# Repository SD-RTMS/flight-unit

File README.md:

# flight-unit

flight unit hardware and software

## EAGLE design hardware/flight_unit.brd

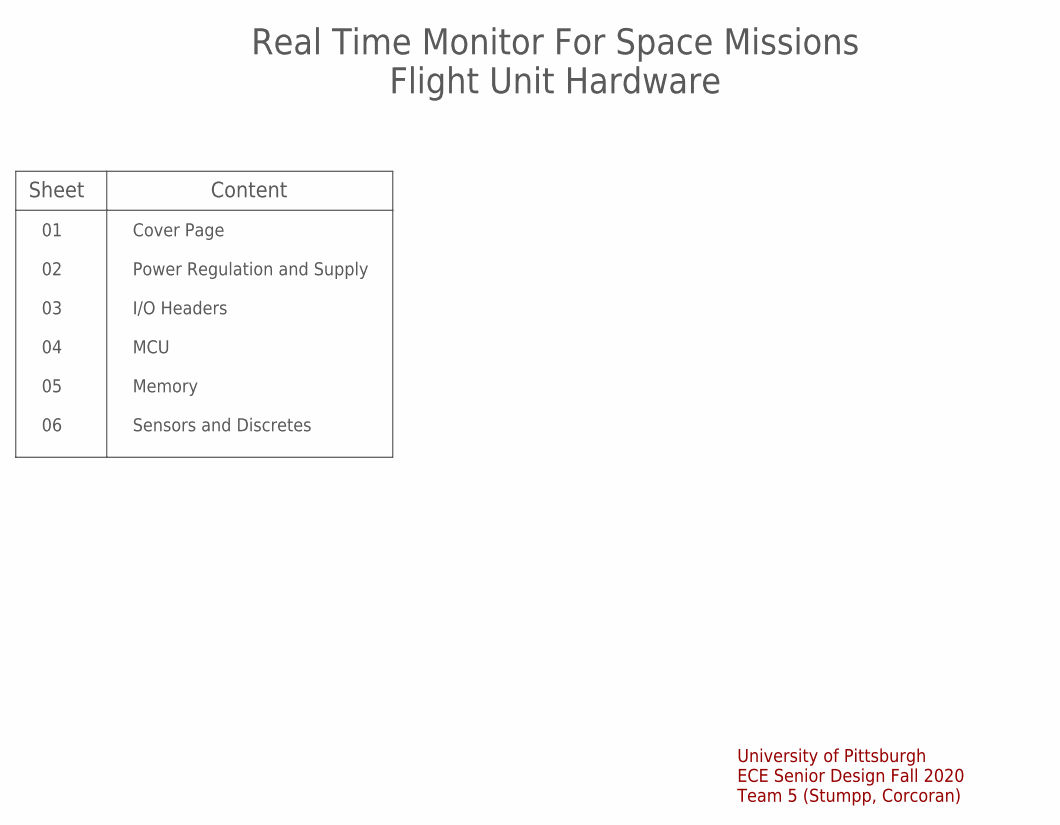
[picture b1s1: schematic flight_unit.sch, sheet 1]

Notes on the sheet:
University of Pittsburgh ECE Senior Design Fall 2020 Team 5 (Stumpp, Corcoran)
Real Time Monitor For Space Missions Flight Unit Hardware
Content
01 02 03 04 05 06
Cover Page Power Regulation and Supply I/O Headers MCU Memory Sensors and Discretes
Sheet

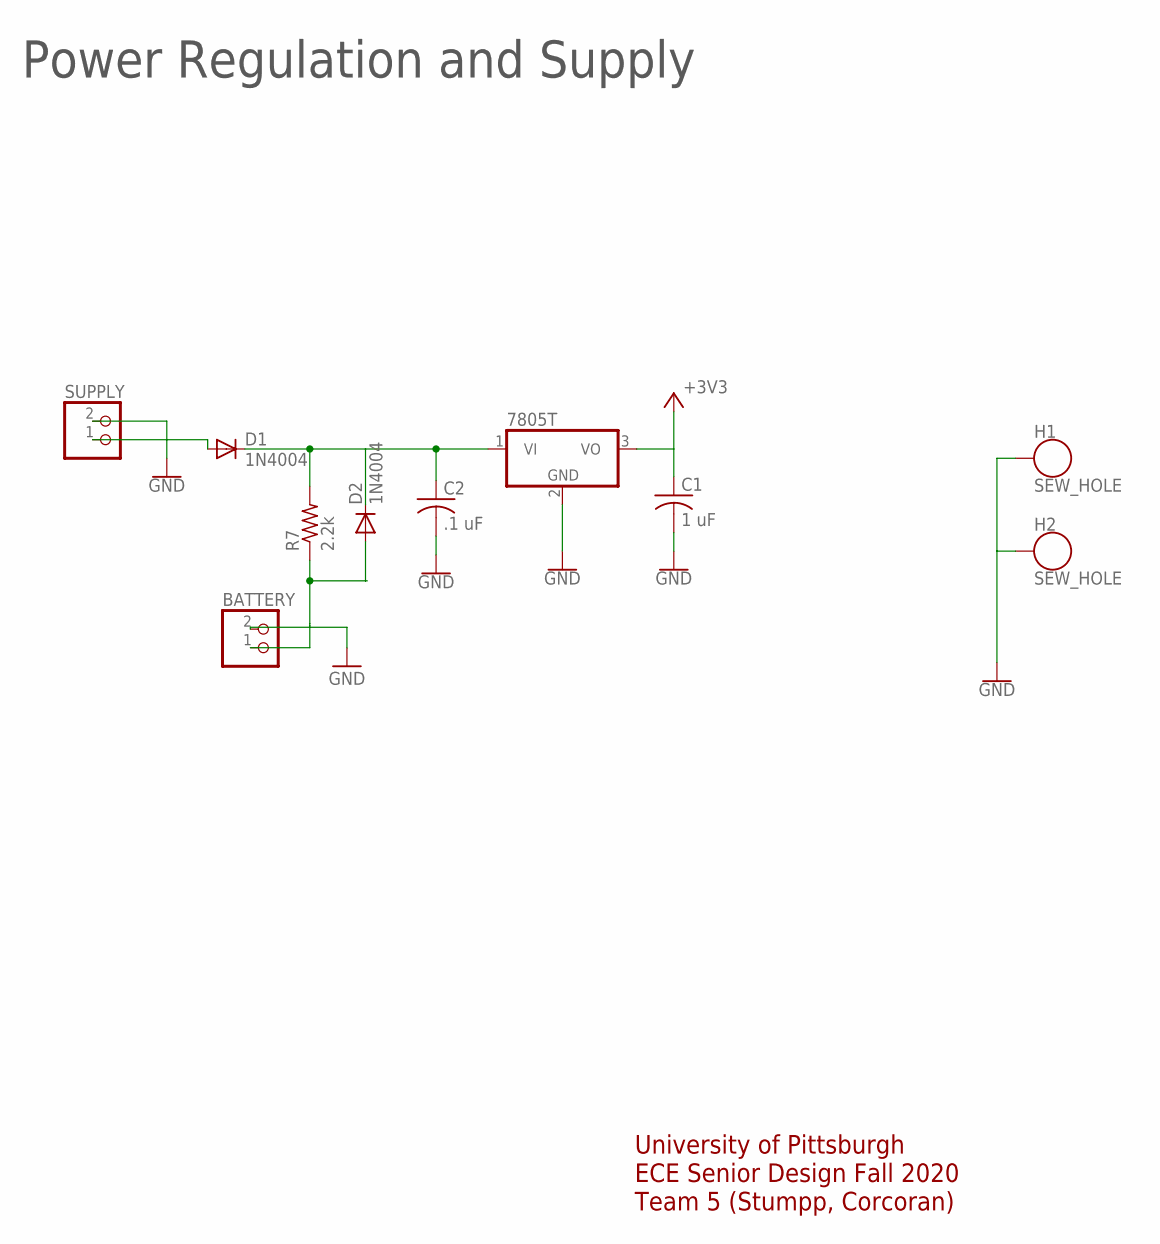
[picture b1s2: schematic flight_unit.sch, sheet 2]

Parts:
BATTERY: JST_2PIN-THM; JST-PH-2-THM
C1: 1 uF; C0805K
C2: .1 uF; C0805K
D1, D2: 1N4004; DO41-10
H1, H2: SEW_HOLE; SIMPLE_HOLE
IC2: 7805T; TO220H
R7: 2.2k; R0805
SUPPLY: JST_2PIN-THM; JST-PH-2-THM

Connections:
+3V3: C1.1, IC2.3 (VO); also elsewhere on the board
GND: BATTERY.2 (1), C1.2, C2.2, H1.P$1, H2.P$1, IC2.2 (GND), SUPPLY.2 (1); also elsewhere on the board
unnamed: BATTERY.1 (2), D2.A, R7.1
unnamed: C2.1, D1.C, D2.C, IC2.1 (VI), R7.2
unnamed: D1.A, SUPPLY.1 (2)

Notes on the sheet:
University of Pittsburgh ECE Senior Design Fall 2020 Team 5 (Stumpp, Corcoran)
Power Regulation and Supply

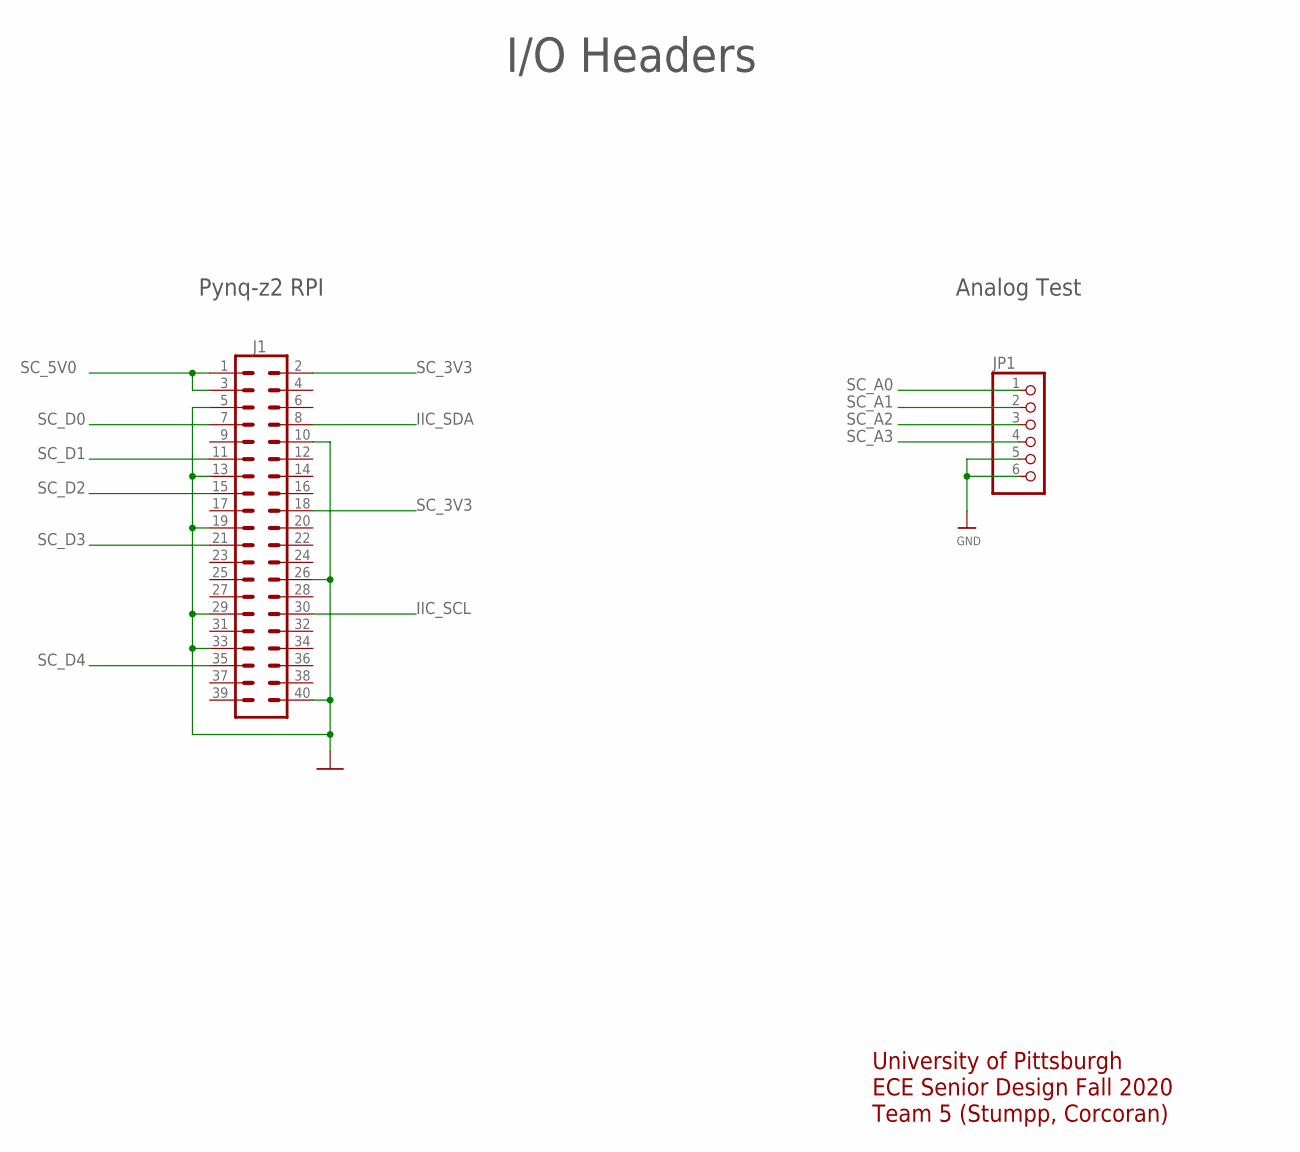
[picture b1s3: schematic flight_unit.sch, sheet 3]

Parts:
J1: CONN_20X2SHROUDED; 2X20_SHROUDED
JP1: PINHD-1X6B; 1X06-BIG

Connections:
GND: J1.5, J1.10, J1.13, J1.19, J1.26, J1.29, J1.33, J1.40, JP1.5, JP1.6; also elsewhere on the board
IIC_SCL: J1.30; also elsewhere on the board
IIC_SDA: J1.8; also elsewhere on the board
SC_3V3: J1.2, J1.18; also elsewhere on the board
SC_5V0: J1.1, J1.3; also elsewhere on the board
SC_A0: JP1.1; also elsewhere on the board
SC_A1: JP1.2; also elsewhere on the board
SC_A2: JP1.3; also elsewhere on the board
SC_A3: JP1.4; also elsewhere on the board
SC_D0: J1.7; also elsewhere on the board
SC_D1: J1.11; also elsewhere on the board
SC_D2: J1.15; also elsewhere on the board
SC_D3: J1.21; also elsewhere on the board
SC_D4: J1.35; also elsewhere on the board

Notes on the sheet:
University of Pittsburgh ECE Senior Design Fall 2020 Team 5 (Stumpp, Corcoran)
I/O Headers
Analog Test
Pynq-z2 RPI

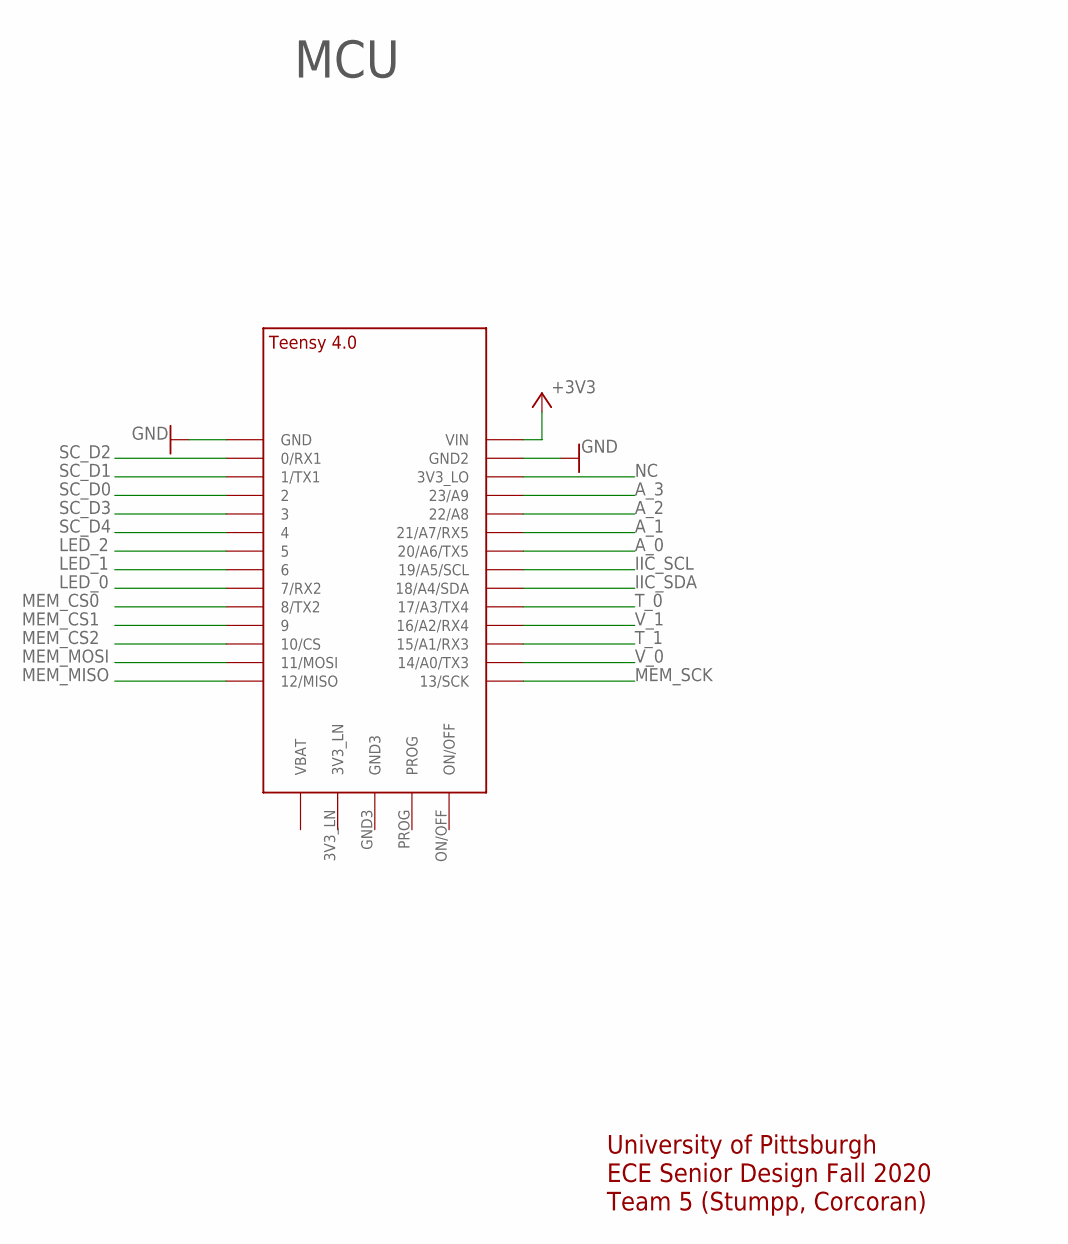
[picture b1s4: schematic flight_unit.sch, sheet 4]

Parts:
U$1: TEENSY_4.0

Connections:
+3V3: U$1.VIN; also elsewhere on the board
A_0: U$1.20/A6 (20/A6/TX5); also elsewhere on the board
A_1: U$1.21/A7 (21/A7/RX5); also elsewhere on the board
A_2: U$1.22/A8; also elsewhere on the board
A_3: U$1.23/A9; also elsewhere on the board
GND: U$1.GND, U$1.GND2; also elsewhere on the board
IIC_SCL: U$1.19/A5/SCL; also elsewhere on the board
IIC_SDA: U$1.18/A4/SDA; also elsewhere on the board
LED_0: U$1.7 (7/RX2); also elsewhere on the board
LED_1: U$1.6; also elsewhere on the board
LED_2: U$1.5; also elsewhere on the board
MEM_CS0: U$1.8 (8/TX2); also elsewhere on the board
MEM_CS1: U$1.9/CS (9); also elsewhere on the board
MEM_CS2: U$1.10/CS; also elsewhere on the board
MEM_MISO: U$1.12/MISO; also elsewhere on the board
MEM_MOSI: U$1.11/MOSI; also elsewhere on the board
MEM_SCK: U$1.13/SCK; also elsewhere on the board
NC: U$1.3V3_LO
SC_D0: U$1.2; also elsewhere on the board
SC_D1: U$1.1/TX (1/TX1); also elsewhere on the board
SC_D2: U$1.0/RX (0/RX1); also elsewhere on the board
SC_D3: U$1.3/CANTX (3); also elsewhere on the board
SC_D4: U$1.4/CANRX (4); also elsewhere on the board
T_0: U$1.17/A3 (17/A3/TX4); also elsewhere on the board
T_1: U$1.15/A1 (15/A1/RX3); also elsewhere on the board
V_0: U$1.14/A0 (14/A0/TX3); also elsewhere on the board
V_1: U$1.16/A2 (16/A2/RX4); also elsewhere on the board

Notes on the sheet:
University of Pittsburgh ECE Senior Design Fall 2020 Team 5 (Stumpp, Corcoran)
MCU

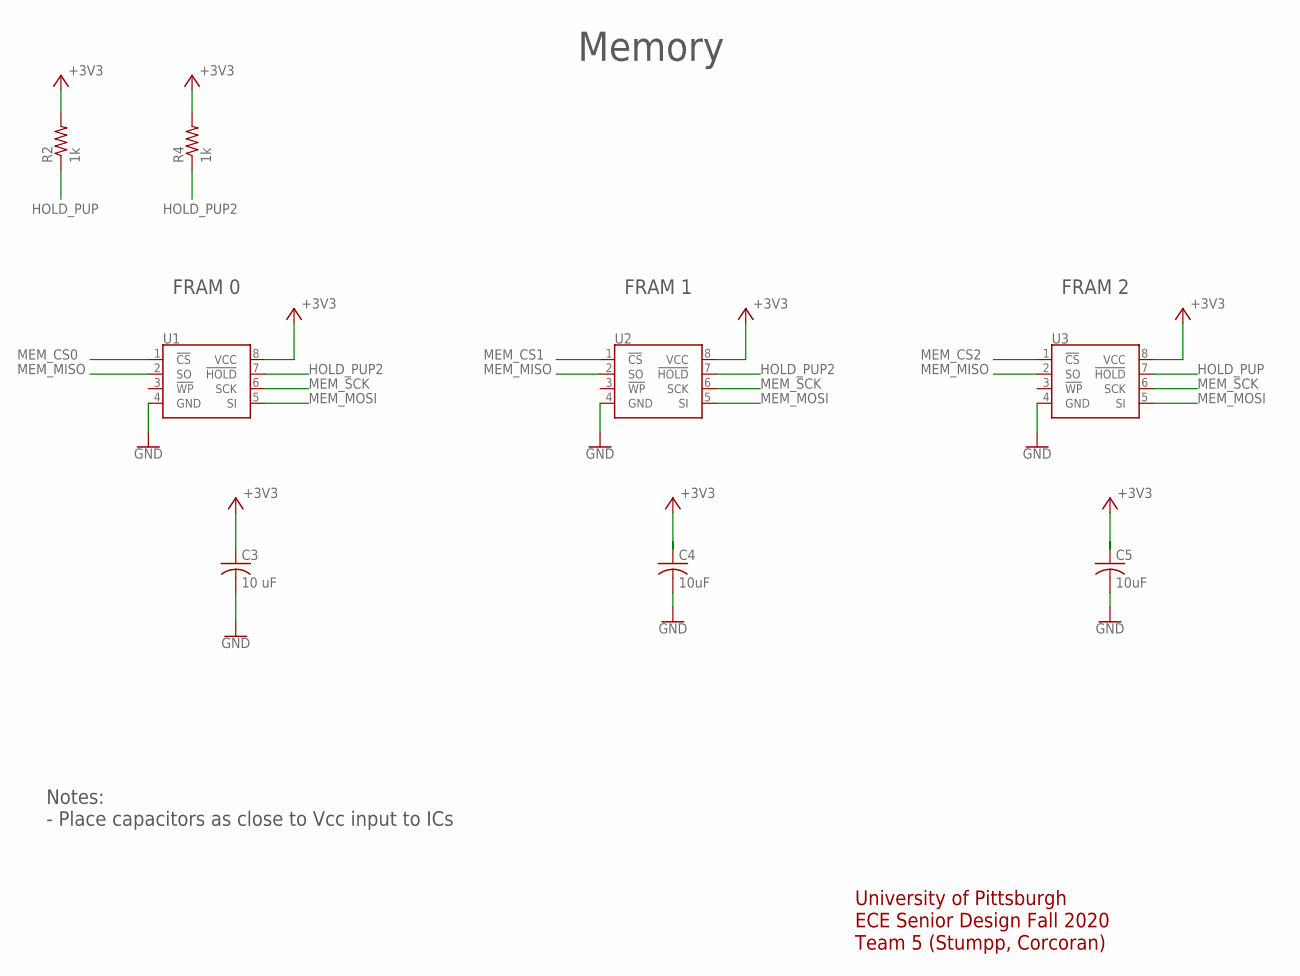
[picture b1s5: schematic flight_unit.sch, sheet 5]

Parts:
C3: 10 uF; C0805K
C4, C5: 10uF; C0805K
R2, R4: 1k; R0805
U1, U2, U3: 4MB Flash; SO08

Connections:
+3V3: C3.1, C4.1, C5.1, R2.2, R4.2, U1.8 (VCC), U2.8 (VCC), U3.8 (VCC); also elsewhere on the board
GND: C3.2, C4.2, C5.2, U1.4 (GND), U2.4 (GND), U3.4 (GND); also elsewhere on the board
HOLD_PUP: R2.1, U3.7 (!HOLD)
HOLD_PUP2: R4.1, U1.7 (!HOLD), U2.7 (!HOLD)
MEM_CS0: U1.1 (!CS); also elsewhere on the board
MEM_CS1: U2.1 (!CS); also elsewhere on the board
MEM_CS2: U3.1 (!CS); also elsewhere on the board
MEM_MISO: U1.2 (SO), U2.2 (SO), U3.2 (SO); also elsewhere on the board
MEM_MOSI: U1.5 (SI), U2.5 (SI), U3.5 (SI); also elsewhere on the board
MEM_SCK: U1.6 (SCK), U2.6 (SCK), U3.6 (SCK); also elsewhere on the board

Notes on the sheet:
University of Pittsburgh ECE Senior Design Fall 2020 Team 5 (Stumpp, Corcoran)
Memory
FRAM 0
FRAM 1
FRAM 2
Notes: - Place capacitors as close to Vcc input to ICs

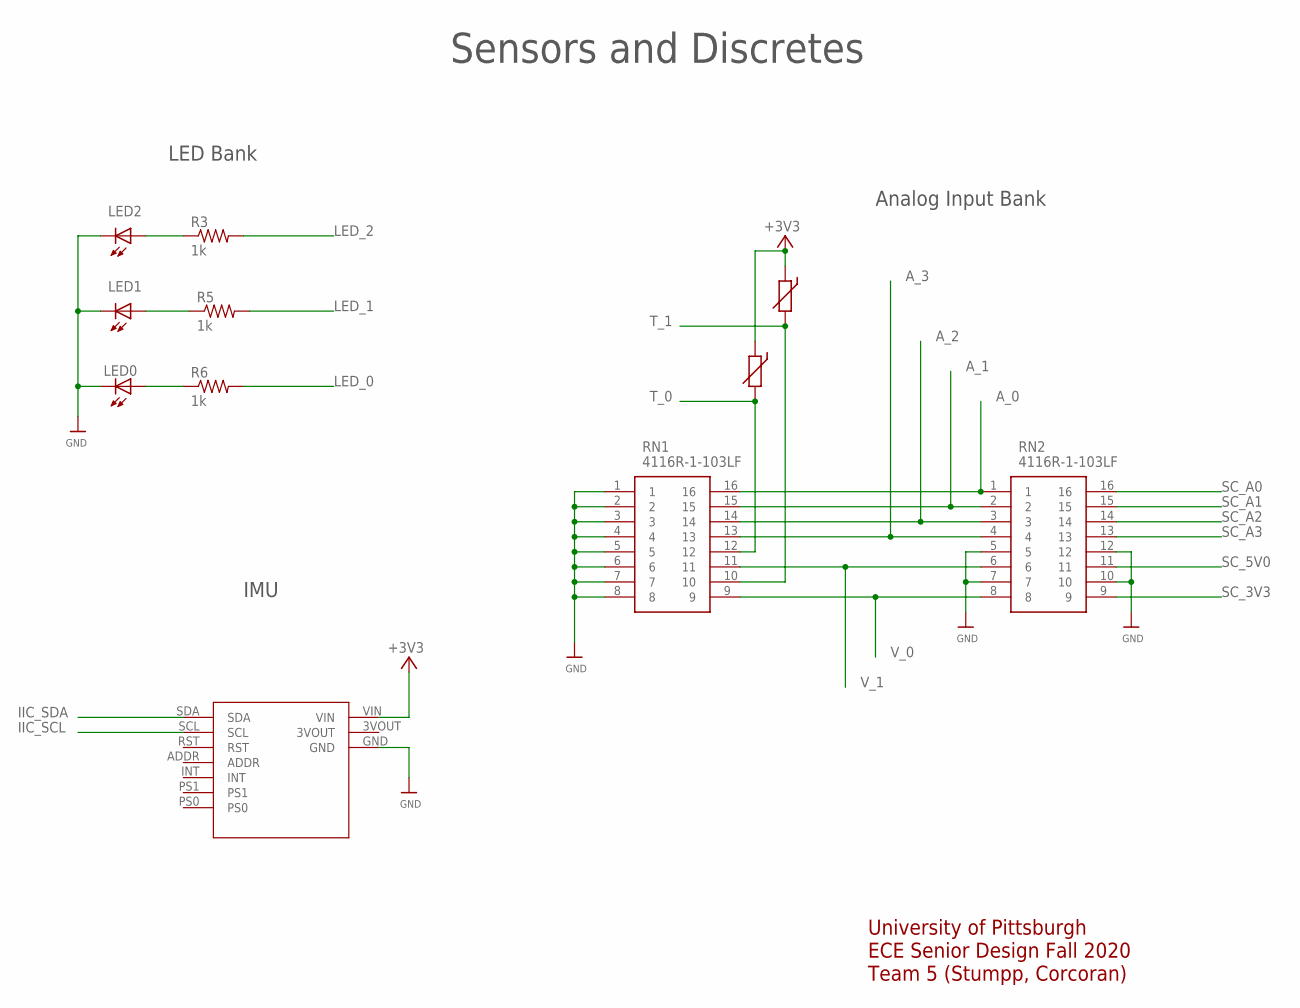
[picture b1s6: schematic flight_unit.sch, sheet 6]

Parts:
LED0, LED1, LED2: LED3MM
R3, R5, R6: 1k; R0805
R8: THERMISTOR-2,5; RS-2,5
RN1, RN2: 4116R-1-103LF; DIP787W49P254L2197H469Q16N
T1: THERMISTOR-2,5; RS-2,5
U$3: IMU_BREAKOUT; BNO055_BREAKOUT

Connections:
+3V3: R8.1, T1.1, U$3.VIN; also elsewhere on the board
A_0: RN1.16, RN2.1; also elsewhere on the board
A_1: RN1.15, RN2.2; also elsewhere on the board
A_2: RN1.14, RN2.3; also elsewhere on the board
A_3: RN1.13, RN2.4; also elsewhere on the board
GND: LED0.K (C), LED1.K (C), LED2.K (C), RN1.1, RN1.2, RN1.3, RN1.4, RN1.5, RN1.6, RN1.7, RN1.8, RN2.5, RN2.7, RN2.10, RN2.12, U$3.GND; also elsewhere on the board
IIC_SCL: U$3.SCL; also elsewhere on the board
IIC_SDA: U$3.SDA; also elsewhere on the board
LED_0: R6.2; also elsewhere on the board
LED_1: R5.2; also elsewhere on the board
LED_2: R3.2; also elsewhere on the board
unnamed: LED2.A, R3.1
unnamed: LED0.A, R6.1
unnamed: LED1.A, R5.1
SC_3V3: RN2.9; also elsewhere on the board
SC_5V0: RN2.11; also elsewhere on the board
SC_A0: RN2.16; also elsewhere on the board
SC_A1: RN2.15; also elsewhere on the board
SC_A2: RN2.14; also elsewhere on the board
SC_A3: RN2.13; also elsewhere on the board
T_0: R8.2, RN1.12; also elsewhere on the board
T_1: RN1.10, T1.2; also elsewhere on the board
V_0: RN1.9, RN2.8; also elsewhere on the board
V_1: RN1.11, RN2.6; also elsewhere on the board

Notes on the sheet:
University of Pittsburgh ECE Senior Design Fall 2020 Team 5 (Stumpp, Corcoran)
Sensors and Discretes
IMU
LED Bank
Analog Input Bank

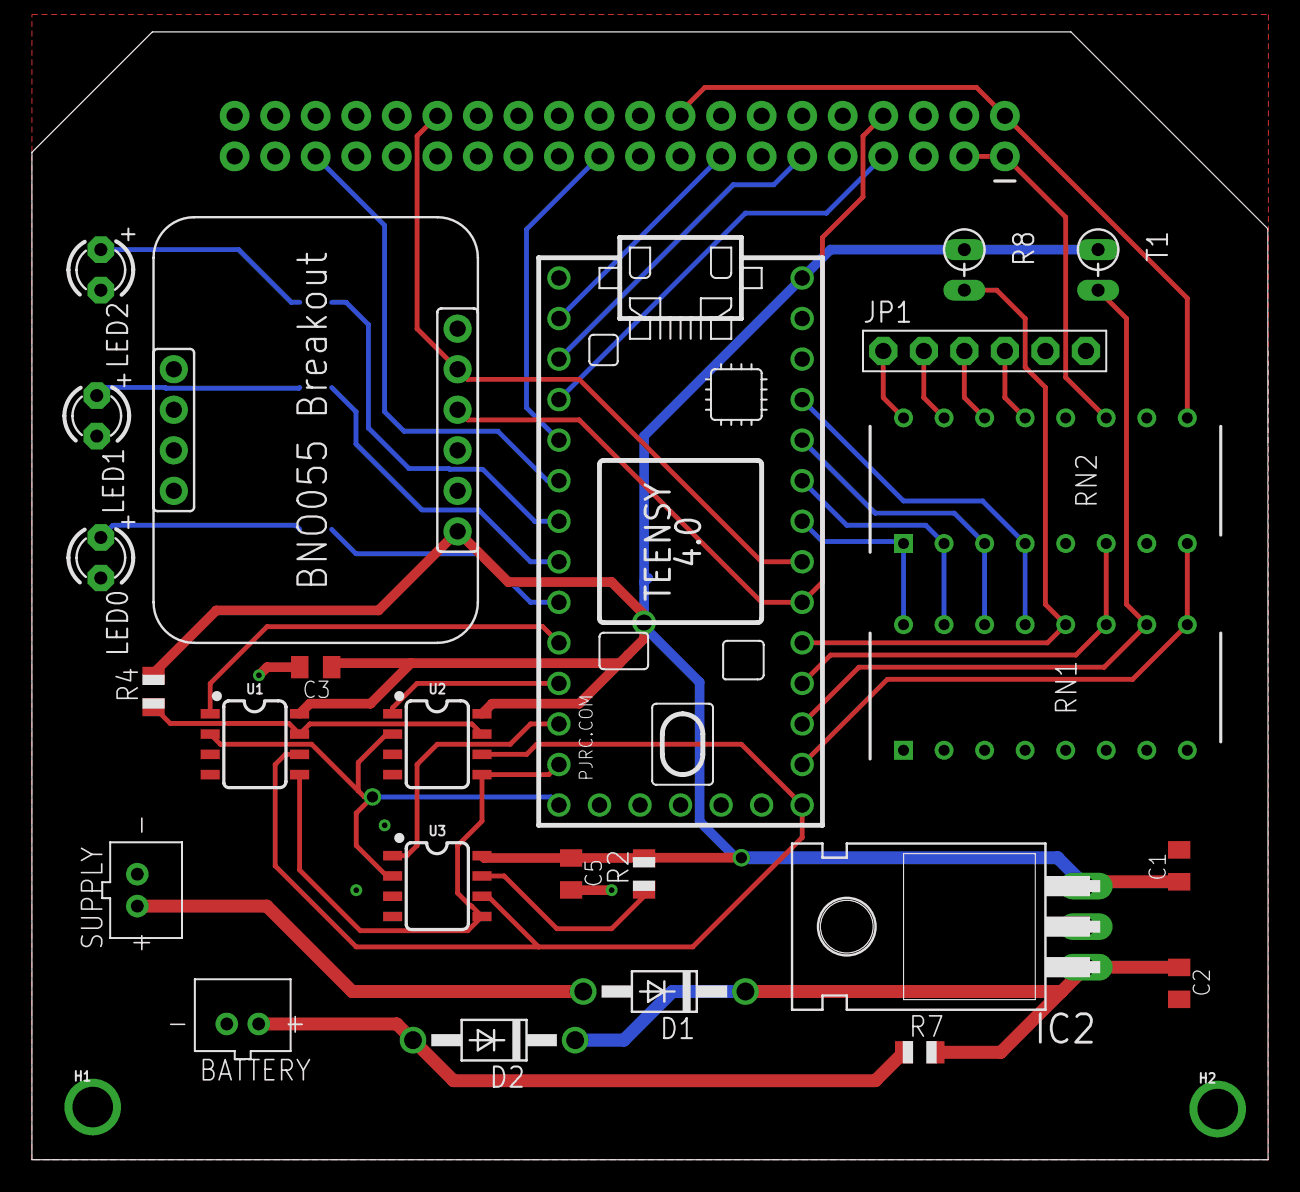
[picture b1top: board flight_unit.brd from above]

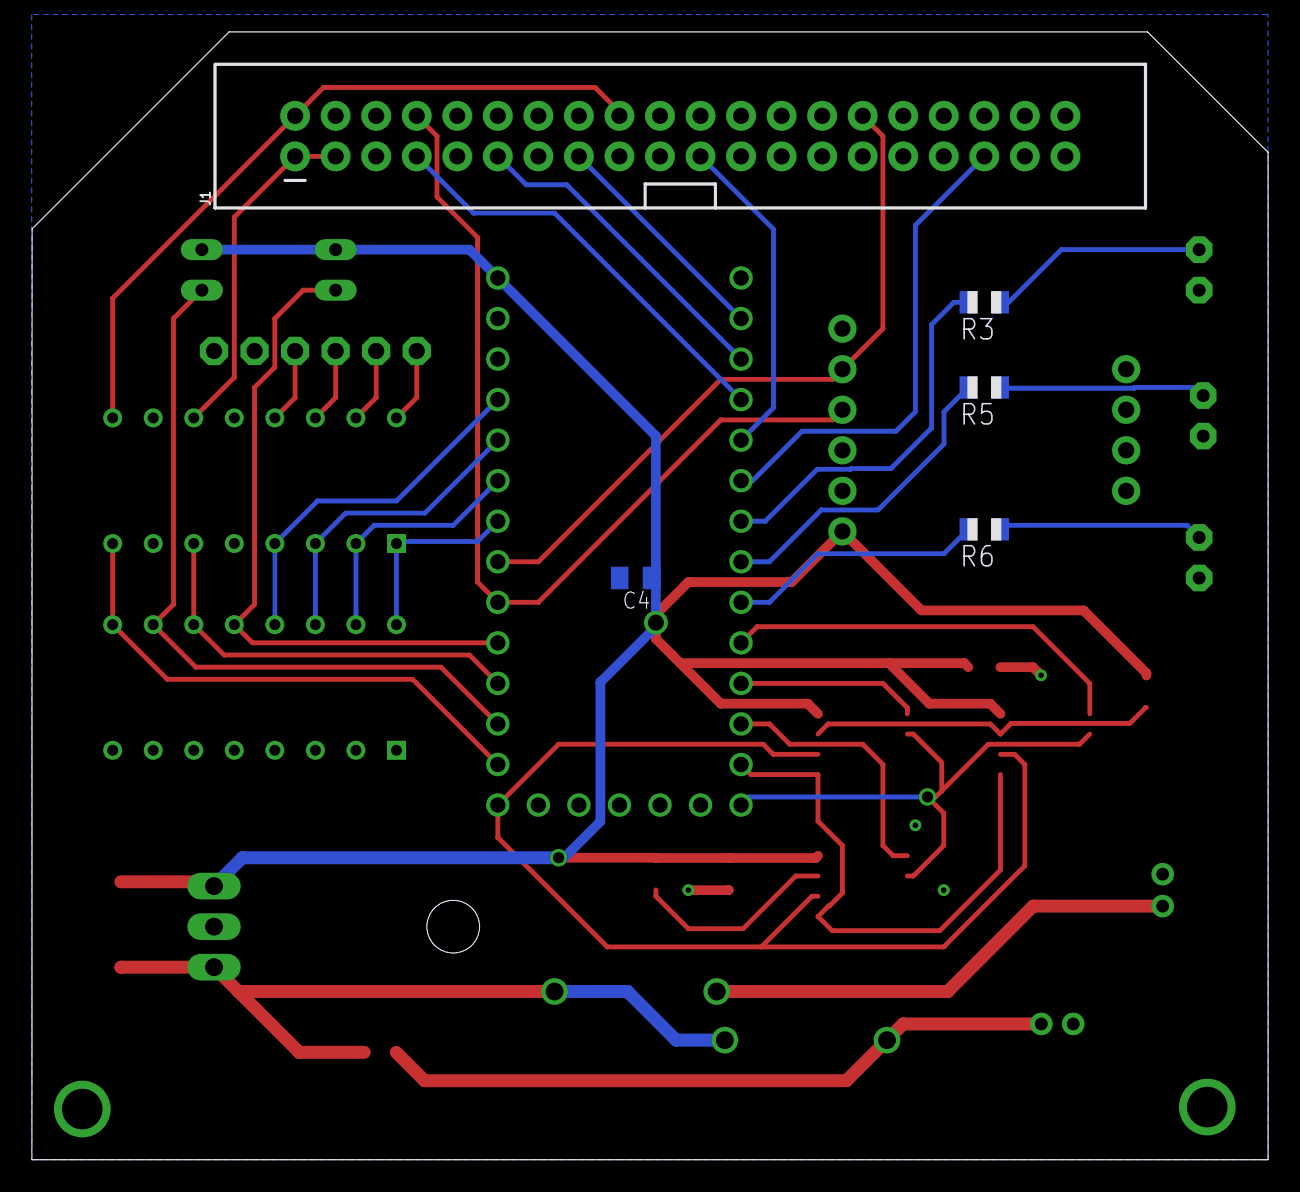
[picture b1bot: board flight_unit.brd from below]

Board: 2 copper layers, 77.5 x 70.7 mm, 32 parts (5 on the bottom side), 40 nets.

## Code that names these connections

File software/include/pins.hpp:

/**
 * @file pins.hpp
 * @author Daniel Stumpp (dcs98@pitt.edu)
 * @brief pin definitions for flight-unit
 * @version 0.1
 * @date 2020-09-18
 * 
 * @copyright Copyright (c) 2020
 * 
 */

#ifndef PINS_HPP
#define PINS_HPP

#define DEBUG false

// Discrete Digital
#define SC_D0 0
#define SC_D1 1
#define SC_D2 2
#define SC_D3 3
#define SC_D4 4

// Discrete Analog
#define A_0 20
#define A_1 21
#define A_2 22
#define A_3 23

// Debug LEDs
#define LED_0 5
#define LED_1 6
#define LED_2 7

// Analog Voltages
#define V_0 14
#define V_1 16

// Analog Temperatures
#define T_0 15
#define T_1 17

// IIC
#define IIC_SCL 19
#define IIC_SDA 18

// SPI
#define MEM_CS0  8
#define MEM_CS1  9
#define MEM_CS2  10
#define MEM_MOSI 11
#define MEM_MISO 12
#define MEM_SCK  13

#endif // PINS_HPP

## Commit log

2020-09-16 updated file structure
2020-09-16 created master schematic
2020-09-17 finished teplate and added pynq-z2 connector
2020-09-17 added fram and MCU
2020-09-18 Added DIP resistor packages for analog bank
2020-09-18 Created and added IMU library part
2020-09-18 updated i/o headers
2020-09-18 PlatformIO project creation
2020-09-18 created pin map header
2020-09-18 added data typedefs
2020-09-18 added comments
2020-09-18 added digital_io class framework
2020-09-20 added start of fram framework
2020-09-21 fix back annotation error
2020-09-21 fixed back annotation error **don't copy and replace the schematic**
2020-09-21 added imu repo as submodule
2020-09-21 accidently deleted this
2020-09-22 Added a bunch of stuff. It builds
2020-09-22 added simple test loop. builds, will test at some point this week
2020-09-22 Added decoupling caps to memory schematic
2020-09-22 updates to schematic and preliminary board work
2020-09-22 working on board layout
2020-09-24 basic stuff to start testing tomorrow
2020-09-24 working on routing...
2020-09-24 few more tweaks.
2020-09-25 timing tweak for testing
2020-09-25 finalized preliminary routing
2020-09-25 changes for demo
2020-10-10 updated git ignore
2020-10-10 added fram functionality, builds, need to do further testing
2020-10-13 Read IMU data
2020-10-14 updates before purchase order
2020-10-19 Basic class declaration for messaging
2020-10-21 Fixed case sensitive includes for linux build
2020-10-21 Initial pb integration
2020-10-21 Add travis-ci support
2020-10-21 Move yml to right spot
2020-10-21 Add build status badge
2020-10-21 Move build script
2020-10-23 Thermistors
    Converts analog signal to thermistor temp readings
2020-10-26 Built message demo
2020-10-29 Some fixes
2020-10-29 Fix build with protobuf
2020-10-29 More CI fixes
2020-10-29 Ci fixes again
2020-11-02 Temporalily add generated protos
2020-11-03 swaped proto structs in for existing data structs, added debug preprocessor statements
2020-11-05 added initial IMU interface as class, fixing previous implementation
2020-11-05 functional fram interface: writes and reads are validated, need to verify higher level dataflow
2020-11-06 bug fixes, fram working
2020-11-06 remove old fix, problem was resolved
2020-11-06 streaming data to serial output when avialable, sufficient to start testing
2020-11-07 added watchdog timer to reset on hangs
2020-11-08 added watchdog and RTC control
2020-11-09 Added Error indicators for initliazing sensors/IOs
    LEDs on board will output binary to indicate which components are not initalizing properly. Wont let system continue unless all are initialized
2020-11-09 Linear and Angular Acceleration Edits
    Added linear acceleration. Changed magnitude to "mag" for magnetization vectors. Added fourth quat_d. Also added linear accleration to proto files
2020-11-09 Update proto
2020-11-09 updated has for power supply
2020-11-09 changes to switch to new proto, test working
2020-11-11 updated mem interface so that delayed metrics will be sent
2020-11-11 it was sending things out backwards. fixed it
2020-11-13 updated comment

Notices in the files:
parts and their libraries:
SparkFun-Connectors: Licensing: Creative Commons ShareAlike 4.0 International - https://creativecommons.org/licenses/by-sa/4.0
